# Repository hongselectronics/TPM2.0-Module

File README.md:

# TPM2.0-Module
A Trusted Platform Module (TPM) breakout board and module compatible with most modern PC motherboards that have a Low Pin Count (LPC) Bus, usually a 20 pin header.  

Hong's Electronics hardware is released under the CERN Permissive V2 License: [CERN-OHL-P V2](https://ohwr.org/cern_ohl_p_v2.txt)

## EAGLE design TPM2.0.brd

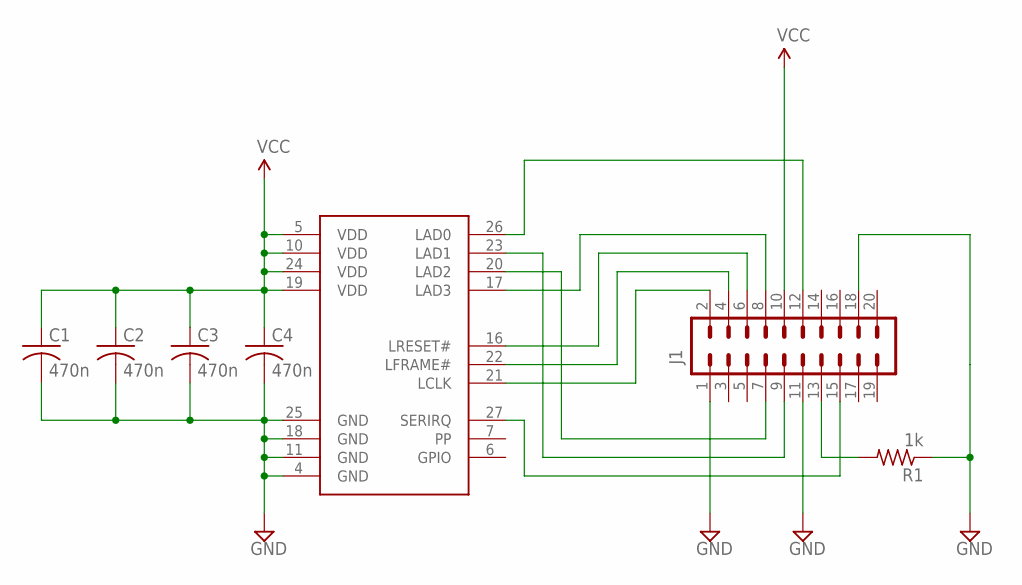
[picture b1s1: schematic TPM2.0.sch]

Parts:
C1, C2, C3, C4: 470n; C0805K
J1: M10X22X10_LOCK; 2X10_LOCK
R1: 1k; R0805
U$1: SLB9965; INF-PG-TSSOP-28-16_M_1PRIMARY

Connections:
GND: C1.2, C2.2, C3.2, C4.2, J1.1, J1.11, J1.18, R1.1, U$1.4 (GND), U$1.11 (GND), U$1.18 (GND), U$1.25 (GND)
unnamed: J1.2, U$1.21 (LCLK)
unnamed: J1.4, U$1.22 (LFRAME#)
unnamed: J1.6, U$1.16 (LRESET#)
unnamed: J1.8, U$1.17 (LAD3)
unnamed: J1.12, U$1.26 (LAD0)
unnamed: J1.7, U$1.20 (LAD2)
unnamed: J1.9, U$1.23 (LAD1)
unnamed: J1.15, U$1.27 (SERIRQ)
unnamed: J1.13, R1.2
VCC: C1.1, C2.1, C3.1, C4.1, J1.10, U$1.5 (VDD), U$1.10 (VDD), U$1.19 (VDD), U$1.24 (VDD)

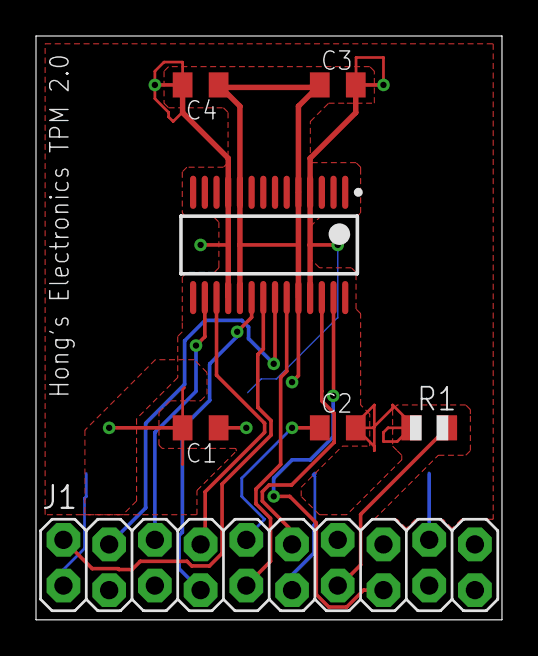
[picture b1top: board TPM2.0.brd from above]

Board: 2 copper layers, 25.9 x 32.4 mm, 7 parts (0 on the bottom side), 11 nets.

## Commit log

2017-06-30 Initial Commit of BRD and SCH files
    First upload of board and schematic files.
2017-06-30 OSHPark rendering
2017-10-12 Added more ground planes
2021-07-08 Create LICENSE.txt
    Update to cern_ohl_p_v2.txt
2021-07-08 Update README.md
    CERN-OHL-P V2 update

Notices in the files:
parts and their libraries:
SparkFun-Connectors: Licensing: Creative Commons ShareAlike 4.0 International - https://creativecommons.org/licenses/by-sa/4.0
